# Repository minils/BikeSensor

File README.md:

# BikeSensor
Bicycle based enviroment sensor

### General

This project was developed at the University of Freiburg. At the chair of [Embedded Systems].

The board that is powered by the wheels of a bicycle is intended to collect sensor data of the enviroment.
This data is then sent via BLE and further processed by an Android smartphone.

### Version
3.2.0

### Setup

What you need to develop:

- [AndroidStudio]
- [Arduino IDE]
- [Eagle CAD]

### Todos

 - Write Tests
 - Improve BLE connection
 - Add sensors

License
----

GPLv2

[//]: # (These are reference links used in the body of this note and get stripped out when the markdown processor does it's job. There is no need to format nicely because it shouldn't be seen. Thanks SO - http://stackoverflow.com/questions/4823468/store-comments-in-markdown-syntax)

   [AndroidStudio]: <https://developer.android.com/sdk/index.html>
   [Arduino IDE]: <https://www.arduino.cc/en/Main/Software>
   [Eagle CAD]: <https://www.cadsoft.de/download-eagle/>
   [Embedded Systems]: <https://earth.informatik.uni-freiburg.de/>

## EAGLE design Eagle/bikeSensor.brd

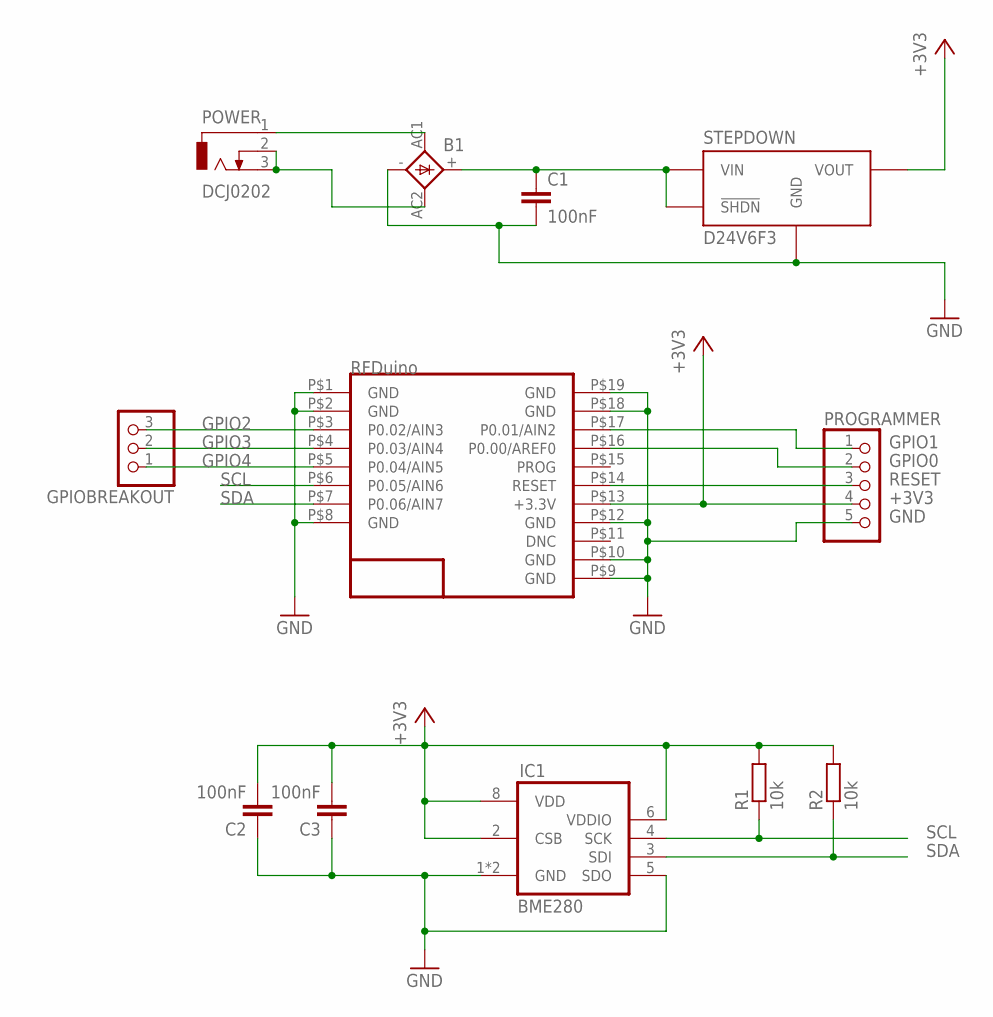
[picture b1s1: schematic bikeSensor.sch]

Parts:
B1: 1KAB
C1: 100nF; C025-050X050
C2, C3: 100nF; C1812
GPIOBREAKOUT: PINHD-1X3; 1X03
IC1: BME280
POWER: DCJ0202
PROGRAMMER: PINHD-1X5; 1X05
R1, R2: 10k; R1206
RFDUINO: RFD22301; RFD21733
STEPDOWN: D24V6F3

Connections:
+3V3: C2.2, C3.2, IC1.2 (CSB), IC1.6 (VDDIO), IC1.8 (VDD), PROGRAMMER.4, R1.2, R2.2, RFDUINO.P$13 (+3.3V), STEPDOWN.VOUT
GND: B1.-, C1.2, C2.1, C3.1, IC1.1 (GND), IC1.5 (SDO), IC1.7 (GND), PROGRAMMER.5, RFDUINO.P$1 (GND), RFDUINO.P$2 (GND), RFDUINO.P$8 (GND), RFDUINO.P$9 (GND), RFDUINO.P$10 (GND), RFDUINO.P$12 (GND), RFDUINO.P$18 (GND), RFDUINO.P$19 (GND), STEPDOWN.GND
GPIO0: PROGRAMMER.2, RFDUINO.P$16 (P0.00/AREF0)
GPIO1: PROGRAMMER.1, RFDUINO.P$17 (P0.01/AIN2)
GPIO2: GPIOBREAKOUT.3, RFDUINO.P$3 (P0.02/AIN3)
GPIO3: GPIOBREAKOUT.2, RFDUINO.P$4 (P0.03/AIN4)
GPIO4: GPIOBREAKOUT.1, RFDUINO.P$5 (P0.04/AIN5)
unnamed: B1.AC2, POWER.2, POWER.3
unnamed: B1.AC1, POWER.1
unnamed: B1.+, C1.1, STEPDOWN.!SHDN, STEPDOWN.VIN
RESET: PROGRAMMER.3, RFDUINO.P$14 (RESET)
SCL: IC1.4 (SCK), R1.1, RFDUINO.P$6 (P0.05/AIN6)
SDA: IC1.3 (SDI), R2.1, RFDUINO.P$7 (P0.06/AIN7)

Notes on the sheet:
RFDuino

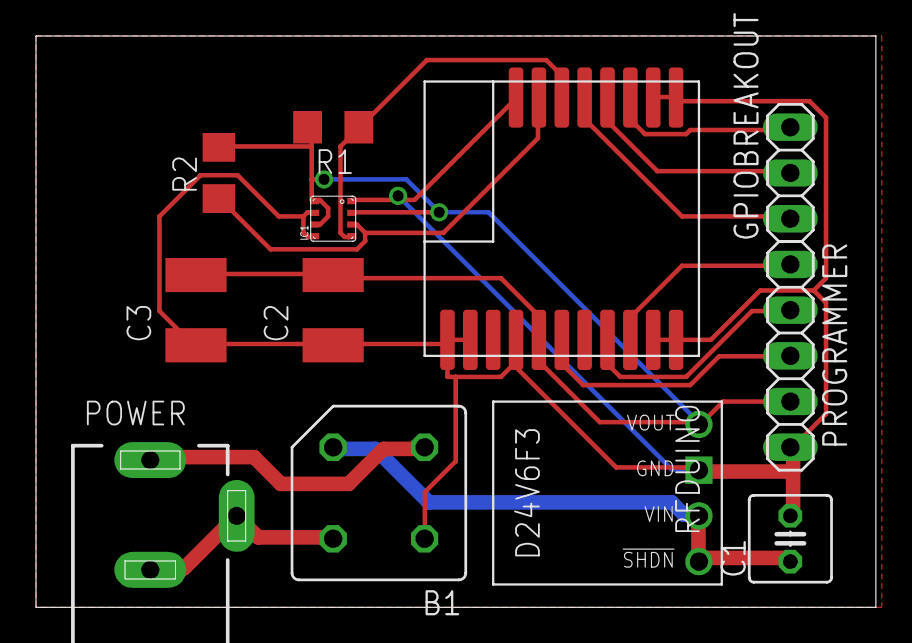
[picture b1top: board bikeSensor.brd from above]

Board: 2 copper layers, 46.7 x 31.7 mm, 12 parts (0 on the bottom side), 13 nets.

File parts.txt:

Pololu 3.3V 600mA Step-Down Spannungsregler D24V6F3
Kondensator	100 µF 35 V
Bosch BME280
Gleichrichter B80C1500 RUND
SMD 1/4W 100K :: SMD-Chip-Widerstand, Bauform 1206, 100 K-Ohm
SMD-1812 100N :: Wima-SMD-Kondensator, Bauform 1812, 100nF
RFD22301 (RFDuino)
BL 1X10G 2,00

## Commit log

2015-10-26 Initial commit of code and resources
2015-10-26 Modify readme
